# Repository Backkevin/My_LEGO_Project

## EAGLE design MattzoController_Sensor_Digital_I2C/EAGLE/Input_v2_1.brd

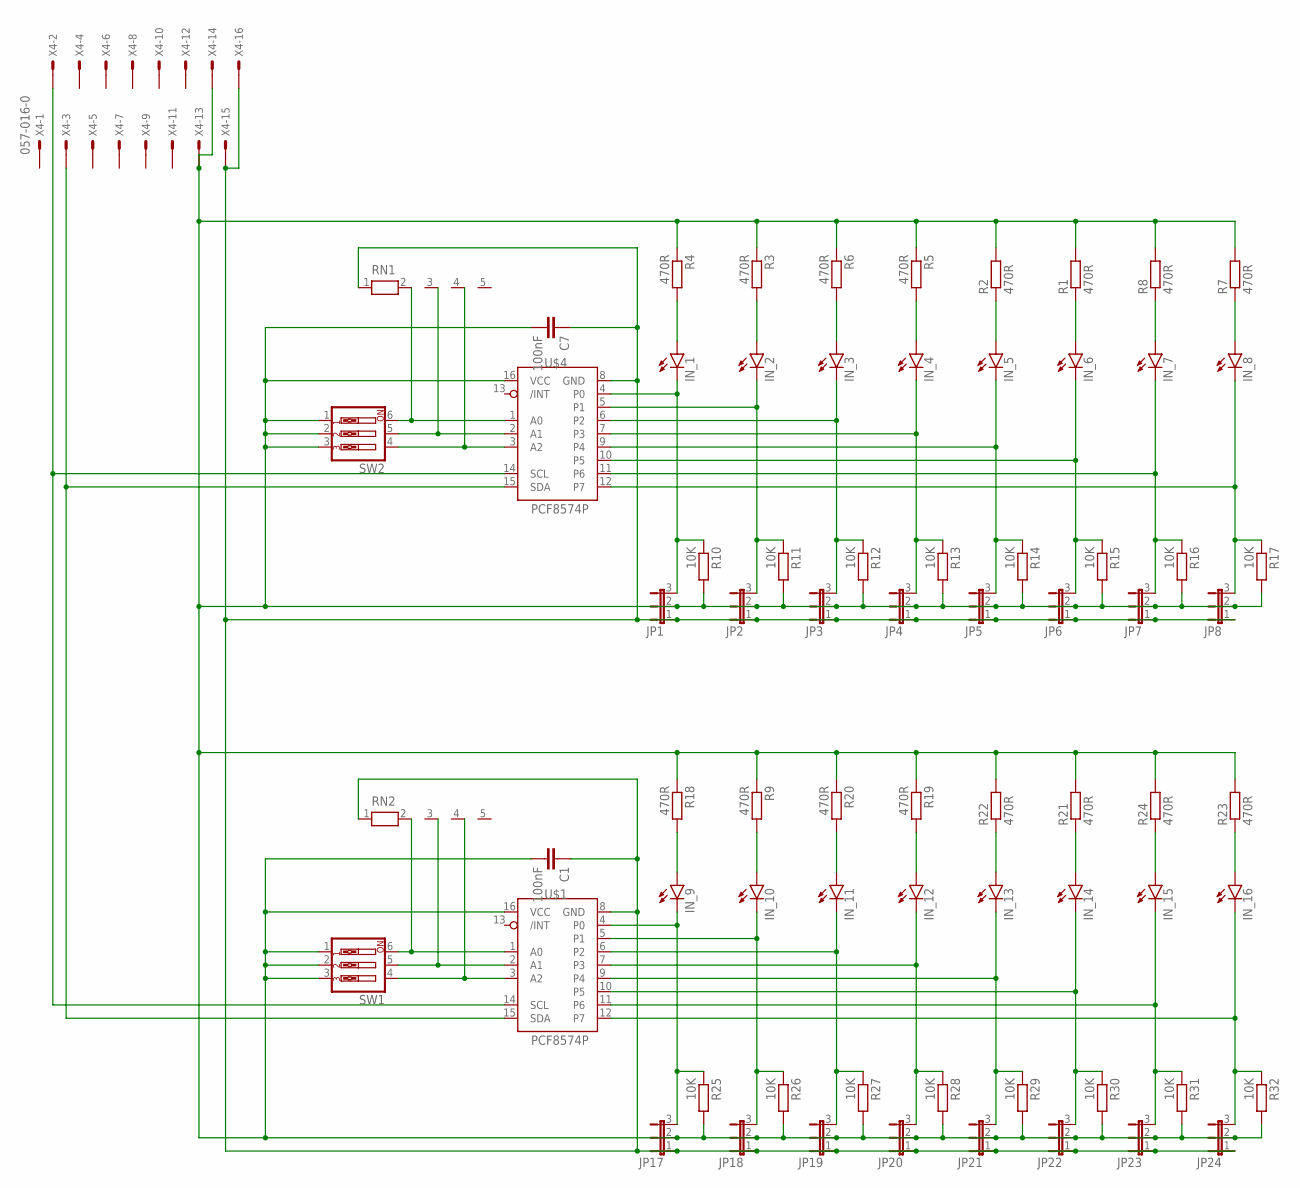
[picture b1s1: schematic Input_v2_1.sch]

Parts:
C1, C7: 100nF; C025-024X044
IN_1, IN_2, IN_3, IN_4, IN_5, IN_6, IN_7, IN_8, IN_9, IN_10, IN_11, IN_12, IN_13, IN_14, IN_15, IN_16: LED3MM
JP1, JP2, JP3, JP4, JP5, JP6, JP7, JP8, JP17, JP18, JP19, JP20, JP21, JP22, JP23, JP24: JP2E; JP2
R1, R2, R3, R4, R5, R6, R7, R8, R9, R18, R19, R20, R21, R22, R23, R24: 470R; 0309/10
R10, R11, R12, R13, R14, R15, R16, R17, R25, R26, R27, R28, R29, R30, R31, R32: 10K; 0309/10
RN1, RN2: RN04; RN-5
SW1, SW2: SW_DIP-3; EDG-03
U$1, U$4: PCF8574P; DIL16
X4: 057-016-0

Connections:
GND2: C1.1, C7.1, JP1.1, JP2.1, JP3.1, JP4.1, JP5.1, JP6.1, JP7.1, JP8.1, JP17.1, JP18.1, JP19.1, JP20.1, JP21.1, JP22.1, JP23.1, JP24.1, RN1.1, RN2.1, U$1.8 (GND), U$4.8 (GND), X4.15, X4.16
unnamed: IN_8.A, R7.1
unnamed: IN_7.A, R8.1
unnamed: IN_6.A, R1.1
unnamed: IN_5.A, R2.1
unnamed: IN_4.A, R5.2
unnamed: IN_3.A, R6.2
unnamed: IN_2.A, R3.2
unnamed: IN_1.A, R4.2
unnamed: RN2.4, SW1.4, U$1.3 (A2)
unnamed: RN2.3, SW1.5, U$1.2 (A1)
unnamed: RN2.2, SW1.6, U$1.1 (A0)
unnamed: RN1.2, SW2.6, U$4.1 (A0)
unnamed: RN1.3, SW2.5, U$4.2 (A1)
unnamed: RN1.4, SW2.4, U$4.3 (A2)
unnamed: IN_9.K (C), JP17.3, R25.1, U$1.4 (P0)
unnamed: IN_10.K (C), JP18.3, R26.1, U$1.5 (P1)
unnamed: IN_11.K (C), JP19.3, R27.1, U$1.6 (P2)
unnamed: IN_1.K (C), JP1.3, R10.1, U$4.4 (P0)
unnamed: IN_2.K (C), JP2.3, R11.1, U$4.5 (P1)
unnamed: IN_3.K (C), JP3.3, R12.1, U$4.6 (P2)
unnamed: IN_4.K (C), JP4.3, R13.1, U$4.7 (P3)
unnamed: IN_5.K (C), JP5.3, R14.1, U$4.9 (P4)
unnamed: IN_6.K (C), JP6.3, R15.1, U$4.10 (P5)
unnamed: IN_7.K (C), JP7.3, R16.1, U$4.11 (P6)
unnamed: IN_8.K (C), JP8.3, R17.1, U$4.12 (P7)
unnamed: IN_12.K (C), JP20.3, R28.1, U$1.7 (P3)
unnamed: IN_13.K (C), JP21.3, R29.1, U$1.9 (P4)
unnamed: IN_14.K (C), JP22.3, R30.1, U$1.10 (P5)
unnamed: IN_15.K (C), JP23.3, R31.1, U$1.11 (P6)
unnamed: IN_16.K (C), JP24.3, R32.1, U$1.12 (P7)
unnamed: IN_16.A, R23.1
unnamed: IN_15.A, R24.1
unnamed: IN_14.A, R21.1
unnamed: IN_13.A, R22.1
unnamed: IN_12.A, R19.2
unnamed: IN_11.A, R20.2
unnamed: IN_10.A, R9.2
unnamed: IN_9.A, R18.2
unnamed: U$1.15 (SDA), U$4.15 (SDA), X4.3
SCL: U$1.14 (SCL), U$4.14 (SCL), X4.2
VCC5.1: C1.2, C7.2, JP1.2, JP2.2, JP3.2, JP4.2, JP5.2, JP6.2, JP7.2, JP8.2, JP17.2, JP18.2, JP19.2, JP20.2, JP21.2, JP22.2, JP23.2, JP24.2, R1.2, R2.2, R3.1, R4.1, R5.1, R6.1, R7.2, R8.2, R9.1, R10.2, R11.2, R12.2, R13.2, R14.2, R15.2, R16.2, R17.2, R18.1, R19.1, R20.1, R21.2, R22.2, R23.2, R24.2, R25.2, R26.2, R27.2, R28.2, R29.2, R30.2, R31.2, R32.2, SW1.1, SW1.2, SW1.3, SW2.1, SW2.2, SW2.3, U$1.16 (VCC), U$4.16 (VCC), X4.13, X4.14

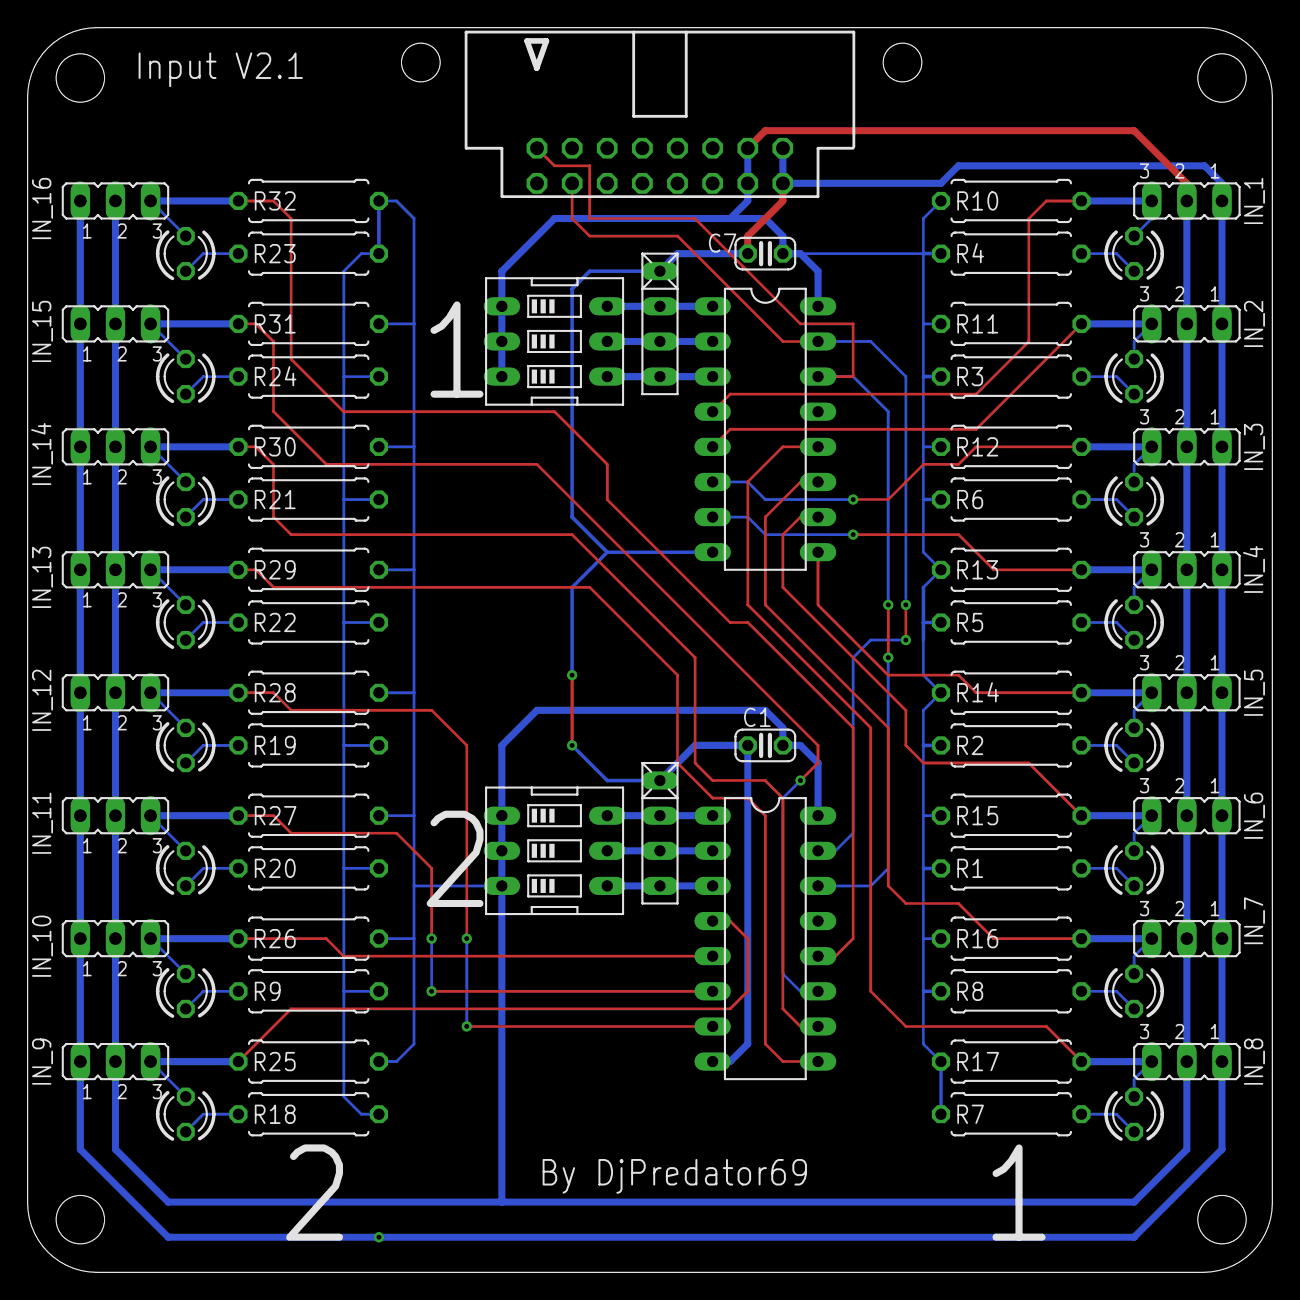
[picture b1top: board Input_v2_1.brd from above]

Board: 2 copper layers, 90.0 x 90.0 mm, 73 parts (0 on the bottom side), 42 nets.

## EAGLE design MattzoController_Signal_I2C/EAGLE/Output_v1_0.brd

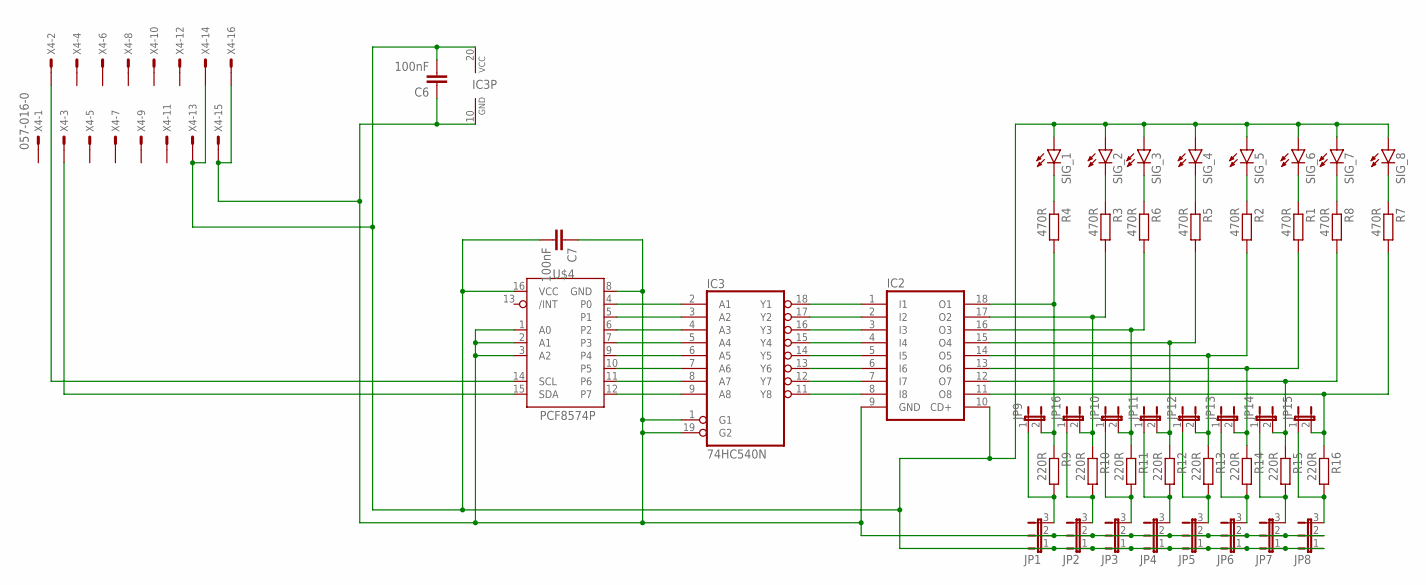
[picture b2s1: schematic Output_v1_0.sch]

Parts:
C6, C7: 100nF; C025-024X044
IC2: ULN2803A; DIL18
IC3: 74HC540N; DIL20
JP1, JP2, JP3, JP4, JP5, JP6, JP7, JP8: JP2E; JP2
JP9, JP10, JP11, JP12, JP13, JP14, JP15, JP16: JP1E; JP1
R1, R2, R3, R4, R5, R6, R7, R8: 470R; 0309/10
R9, R10, R11, R12, R13, R14, R15, R16: 220R; 0309/10
SIG_1, SIG_2, SIG_3, SIG_4, SIG_5, SIG_6, SIG_7, SIG_8: LED3MM
U$4: PCF8574P; DIL16
X4: 057-016-0

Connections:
GND1: C6.1, C7.1, IC2.9 (GND), IC3.1 (G1), IC3.10 (GND), IC3.19 (G2), JP1.2, JP2.2, JP3.2, JP4.2, JP5.2, JP6.2, JP7.2, JP8.2, U$4.1 (A0), U$4.2 (A1), U$4.3 (A2), U$4.8 (GND), X4.15, X4.16
unnamed: JP1.3, JP9.1, R9.2
unnamed: IC2.13 (O6), JP13.2, R1.2, R14.1
unnamed: R2.1, SIG_5.K (C)
unnamed: R1.1, SIG_6.K (C)
unnamed: IC2.12 (O7), JP14.2, R8.2, R15.1
unnamed: U$4.15 (SDA), X4.3
unnamed: R8.1, SIG_7.K (C)
unnamed: R7.1, SIG_8.K (C)
unnamed: JP2.3, JP16.1, R10.2
unnamed: JP3.3, JP10.1, R11.2
unnamed: JP4.3, JP11.1, R12.2
unnamed: IC2.8 (I8), IC3.11 (Y8)
unnamed: JP5.3, JP12.1, R13.2
unnamed: IC2.7 (I7), IC3.12 (Y7)
unnamed: IC2.6 (I6), IC3.13 (Y6)
unnamed: IC2.5 (I5), IC3.14 (Y5)
unnamed: IC2.4 (I4), IC3.15 (Y4)
unnamed: IC2.3 (I3), IC3.16 (Y3)
unnamed: IC2.2 (I2), IC3.17 (Y2)
unnamed: IC2.1 (I1), IC3.18 (Y1)
unnamed: IC3.2 (A1), U$4.4 (P0)
unnamed: IC3.3 (A2), U$4.5 (P1)
unnamed: IC3.4 (A3), U$4.6 (P2)
unnamed: IC3.5 (A4), U$4.7 (P3)
unnamed: IC3.6 (A5), U$4.9 (P4)
unnamed: IC3.7 (A6), U$4.10 (P5)
unnamed: IC3.8 (A7), U$4.11 (P6)
unnamed: IC3.9 (A8), U$4.12 (P7)
unnamed: IC2.18 (O1), JP9.2, R4.2, R9.1
unnamed: JP6.3, JP13.1, R14.2
unnamed: IC2.17 (O2), JP16.2, R3.2, R10.1
unnamed: JP7.3, JP14.1, R15.2
unnamed: JP8.3, JP15.1, R16.2
unnamed: U$4.14 (SCL), X4.2
unnamed: R4.1, SIG_1.K (C)
unnamed: R3.1, SIG_2.K (C)
unnamed: IC2.11 (O8), JP15.2, R7.2, R16.1
unnamed: IC2.16 (O3), JP10.2, R6.2, R11.1
unnamed: IC2.15 (O4), JP11.2, R5.2, R12.1
unnamed: IC2.14 (O5), JP12.2, R2.2, R13.1
unnamed: R6.1, SIG_3.K (C)
unnamed: R5.1, SIG_4.K (C)
VCC5.0: C6.2, C7.2, IC2.10 (CD+), IC3.20 (VCC), JP1.1, JP2.1, JP3.1, JP4.1, JP5.1, JP6.1, JP7.1, JP8.1, SIG_1.A, SIG_2.A, SIG_3.A, SIG_4.A, SIG_5.A, SIG_6.A, SIG_7.A, SIG_8.A, U$4.16 (VCC), X4.13, X4.14

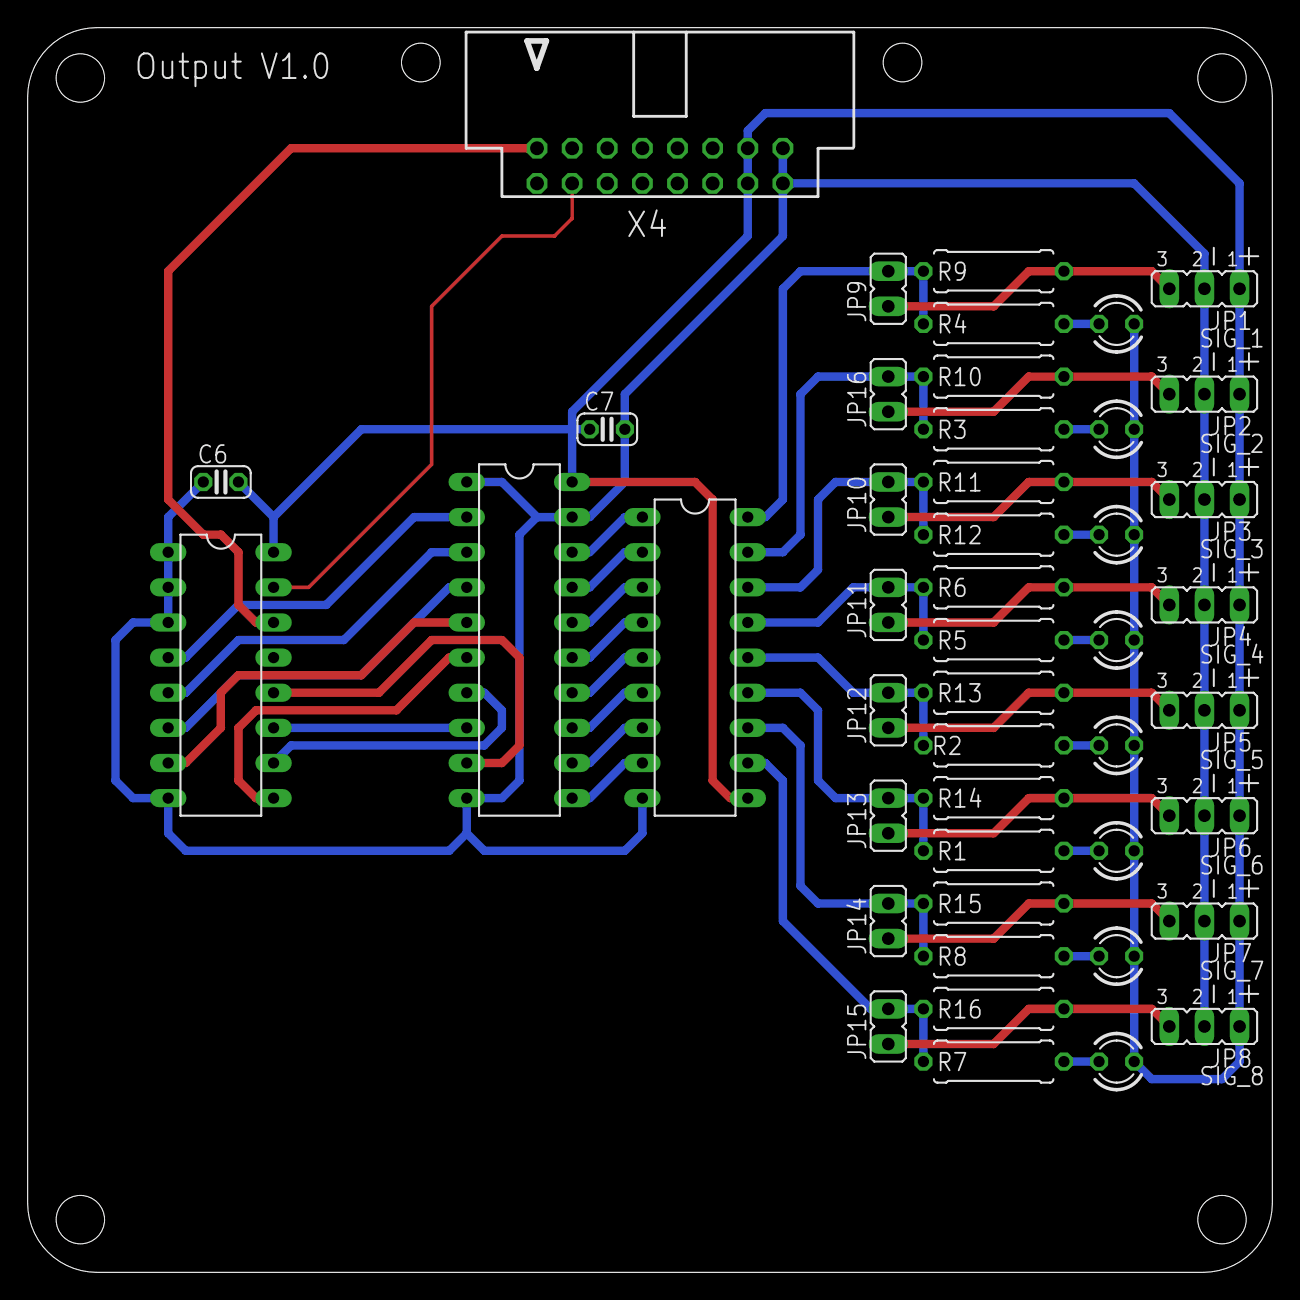
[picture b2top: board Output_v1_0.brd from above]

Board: 2 copper layers, 90.0 x 90.0 mm, 46 parts (0 on the bottom side), 44 nets.

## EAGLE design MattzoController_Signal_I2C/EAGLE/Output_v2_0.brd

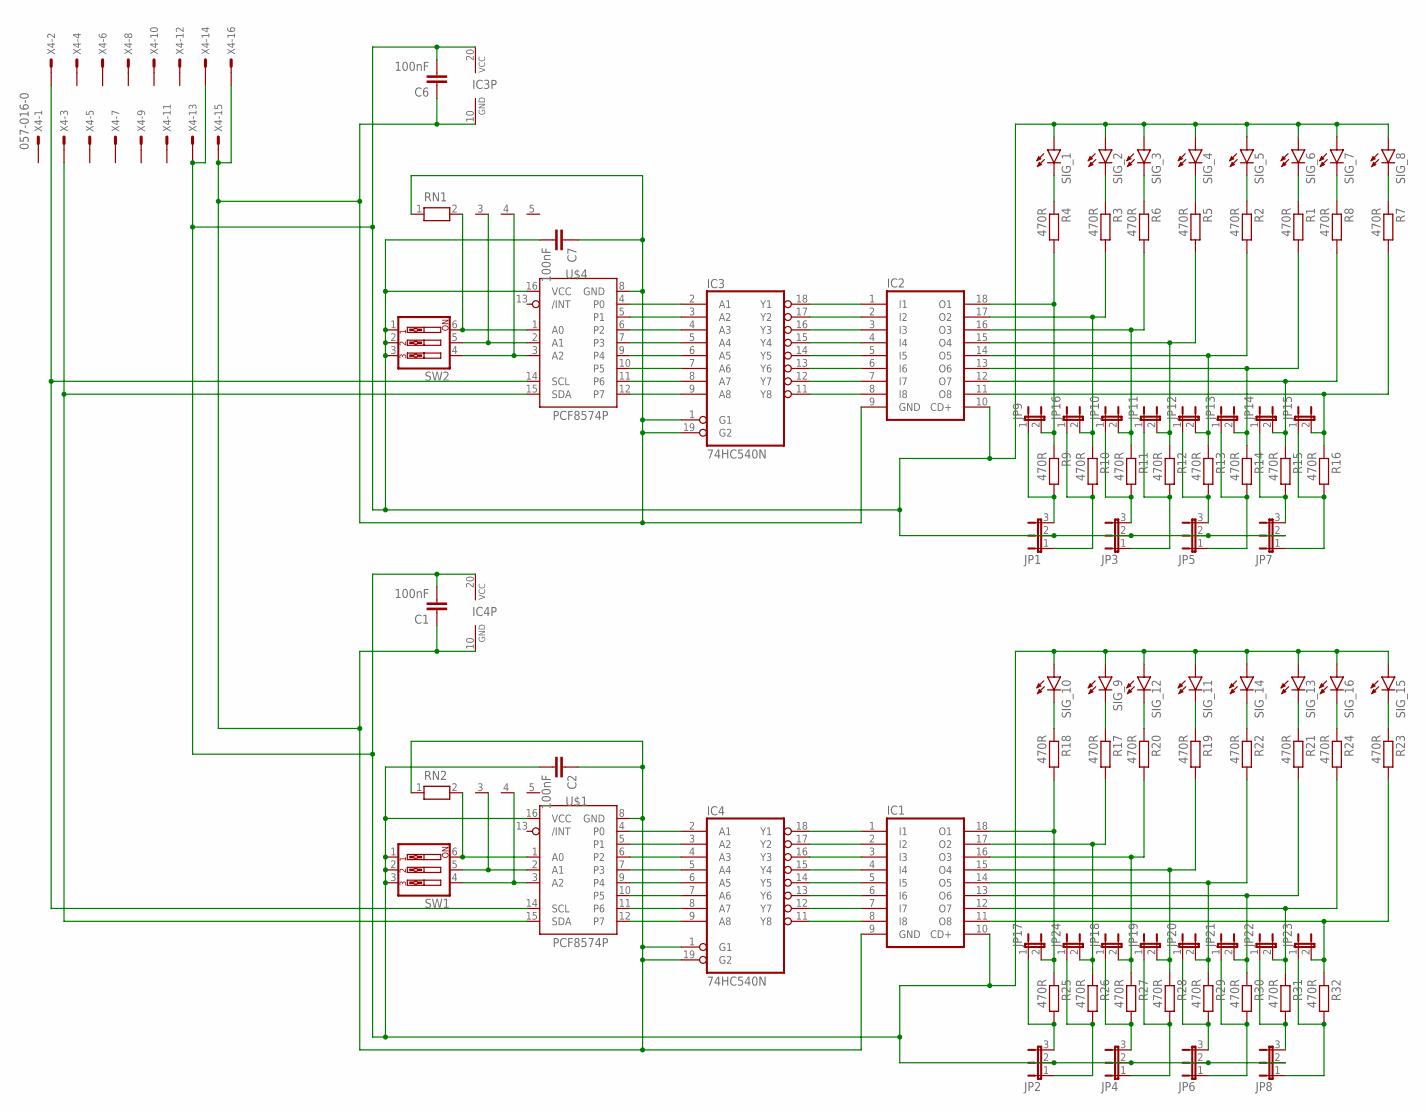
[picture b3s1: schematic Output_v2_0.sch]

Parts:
C1, C2, C6, C7: 100nF; C025-024X044
IC1, IC2: ULN2803A; DIL18
IC3, IC4: 74HC540N; DIL20
JP1, JP2, JP3, JP4, JP5, JP6, JP7, JP8: JP2E; JP2
JP9, JP10, JP11, JP12, JP13, JP14, JP15, JP16, JP17, JP18, JP19, JP20, JP21, JP22, JP23, JP24: JP1E; JP1
R1, R2, R3, R4, R5, R6, R7, R8, R9, R10, R11, R12, R13, R14, R15, R16, R17, R18, R19, R20, R21, R22, R23, R24, R25, R26, R27, R28, R29, R30, R31, R32: 470R; 0309/10
RN1, RN2: RN04; RN-5
SIG_1, SIG_2, SIG_3, SIG_4, SIG_5, SIG_6, SIG_7, SIG_8, SIG_9, SIG_10, SIG_11, SIG_12, SIG_13, SIG_14, SIG_15, SIG_16: LED3MM
SW1, SW2: SW_DIP-3; EDG-03
U$1, U$4: PCF8574P; DIL16
X4: 057-016-0

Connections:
GND2: C1.1, C2.1, C6.1, C7.1, IC1.9 (GND), IC2.9 (GND), IC3.1 (G1), IC3.10 (GND), IC3.19 (G2), IC4.1 (G1), IC4.10 (GND), IC4.19 (G2), RN1.1, RN2.1, U$1.8 (GND), U$4.8 (GND), X4.15, X4.16
unnamed: JP1.3, JP9.1, R9.2
unnamed: IC2.13 (O6), JP13.2, R1.2, R14.1
unnamed: R2.1, SIG_5.K (C)
unnamed: R1.1, SIG_6.K (C)
unnamed: IC2.12 (O7), JP14.2, R8.2, R15.1
unnamed: RN2.4, SW1.4, U$1.3 (A2)
unnamed: R8.1, SIG_7.K (C)
unnamed: R7.1, SIG_8.K (C)
unnamed: JP1.1, JP16.1, R10.2
unnamed: JP3.3, JP10.1, R11.2
unnamed: JP3.1, JP11.1, R12.2
unnamed: IC2.8 (I8), IC3.11 (Y8)
unnamed: JP5.3, JP12.1, R13.2
unnamed: IC2.7 (I7), IC3.12 (Y7)
unnamed: IC2.6 (I6), IC3.13 (Y6)
unnamed: IC2.5 (I5), IC3.14 (Y5)
unnamed: IC2.4 (I4), IC3.15 (Y4)
unnamed: IC2.3 (I3), IC3.16 (Y3)
unnamed: IC2.2 (I2), IC3.17 (Y2)
unnamed: IC2.1 (I1), IC3.18 (Y1)
unnamed: IC3.2 (A1), U$4.4 (P0)
unnamed: IC3.3 (A2), U$4.5 (P1)
unnamed: IC3.4 (A3), U$4.6 (P2)
unnamed: IC3.5 (A4), U$4.7 (P3)
unnamed: IC3.6 (A5), U$4.9 (P4)
unnamed: IC3.7 (A6), U$4.10 (P5)
unnamed: IC3.8 (A7), U$4.11 (P6)
unnamed: IC3.9 (A8), U$4.12 (P7)
unnamed: IC2.18 (O1), JP9.2, R4.2, R9.1
unnamed: JP5.1, JP13.1, R14.2
unnamed: IC2.17 (O2), JP16.2, R3.2, R10.1
unnamed: JP7.3, JP14.1, R15.2
unnamed: JP7.1, JP15.1, R16.2
unnamed: IC1.8 (I8), IC4.11 (Y8)
unnamed: RN2.3, SW1.5, U$1.2 (A1)
unnamed: R4.1, SIG_1.K (C)
unnamed: R3.1, SIG_2.K (C)
unnamed: IC2.11 (O8), JP15.2, R7.2, R16.1
unnamed: IC1.7 (I7), IC4.12 (Y7)
unnamed: IC1.6 (I6), IC4.13 (Y6)
unnamed: IC2.16 (O3), JP10.2, R6.2, R11.1
unnamed: IC2.15 (O4), JP11.2, R5.2, R12.1
unnamed: IC2.14 (O5), JP12.2, R2.2, R13.1
unnamed: IC1.5 (I5), IC4.14 (Y5)
unnamed: IC1.4 (I4), IC4.15 (Y4)
unnamed: IC1.3 (I3), IC4.16 (Y3)
unnamed: IC1.2 (I2), IC4.17 (Y2)
unnamed: IC1.1 (I1), IC4.18 (Y1)
unnamed: IC4.2 (A1), U$1.4 (P0)
unnamed: IC4.3 (A2), U$1.5 (P1)
unnamed: IC4.4 (A3), U$1.6 (P2)
unnamed: IC4.5 (A4), U$1.7 (P3)
unnamed: R6.1, SIG_3.K (C)
unnamed: R5.1, SIG_4.K (C)
unnamed: IC4.6 (A5), U$1.9 (P4)
unnamed: IC4.7 (A6), U$1.10 (P5)
unnamed: IC4.8 (A7), U$1.11 (P6)
unnamed: IC4.9 (A8), U$1.12 (P7)
unnamed: IC1.18 (O1), JP17.2, R18.2, R25.1
unnamed: IC1.17 (O2), JP24.2, R17.2, R26.1
unnamed: R18.1, SIG_10.K (C)
unnamed: R17.1, SIG_9.K (C)
unnamed: IC1.16 (O3), JP18.2, R20.2, R27.1
unnamed: IC1.15 (O4), JP19.2, R19.2, R28.1
unnamed: IC1.14 (O5), JP20.2, R22.2, R29.1
unnamed: R20.1, SIG_12.K (C)
unnamed: R19.1, SIG_11.K (C)
unnamed: IC1.13 (O6), JP21.2, R21.2, R30.1
unnamed: R22.1, SIG_14.K (C)
unnamed: R21.1, SIG_13.K (C)
unnamed: IC1.12 (O7), JP22.2, R24.2, R31.1
unnamed: R24.1, SIG_16.K (C)
unnamed: R23.1, SIG_15.K (C)
unnamed: JP2.3, JP17.1, R25.2
unnamed: JP2.1, JP24.1, R26.2
unnamed: JP4.3, JP18.1, R27.2
unnamed: JP4.1, JP19.1, R28.2
unnamed: JP6.3, JP20.1, R29.2
unnamed: JP6.1, JP21.1, R30.2
unnamed: JP8.3, JP22.1, R31.2
unnamed: JP8.1, JP23.1, R32.2
unnamed: U$1.14 (SCL), U$4.14 (SCL), X4.2
unnamed: IC1.11 (O8), JP23.2, R23.2, R32.1
unnamed: U$1.15 (SDA), U$4.15 (SDA), X4.3
unnamed: RN2.2, SW1.6, U$1.1 (A0)
unnamed: RN1.2, SW2.6, U$4.1 (A0)
unnamed: RN1.3, SW2.5, U$4.2 (A1)
unnamed: RN1.4, SW2.4, U$4.3 (A2)
VCC5.1: C1.2, C2.2, C6.2, C7.2, IC1.10 (CD+), IC2.10 (CD+), IC3.20 (VCC), IC4.20 (VCC), JP1.2, JP2.2, JP3.2, JP4.2, JP5.2, JP6.2, JP7.2, JP8.2, SIG_1.A, SIG_2.A, SIG_3.A, SIG_4.A, SIG_5.A, SIG_6.A, SIG_7.A, SIG_8.A, SIG_9.A, SIG_10.A, SIG_11.A, SIG_12.A, SIG_13.A, SIG_14.A, SIG_15.A, SIG_16.A, SW1.1, SW1.2, SW1.3, SW2.1, SW2.2, SW2.3, U$1.16 (VCC), U$4.16 (VCC), X4.13, X4.14

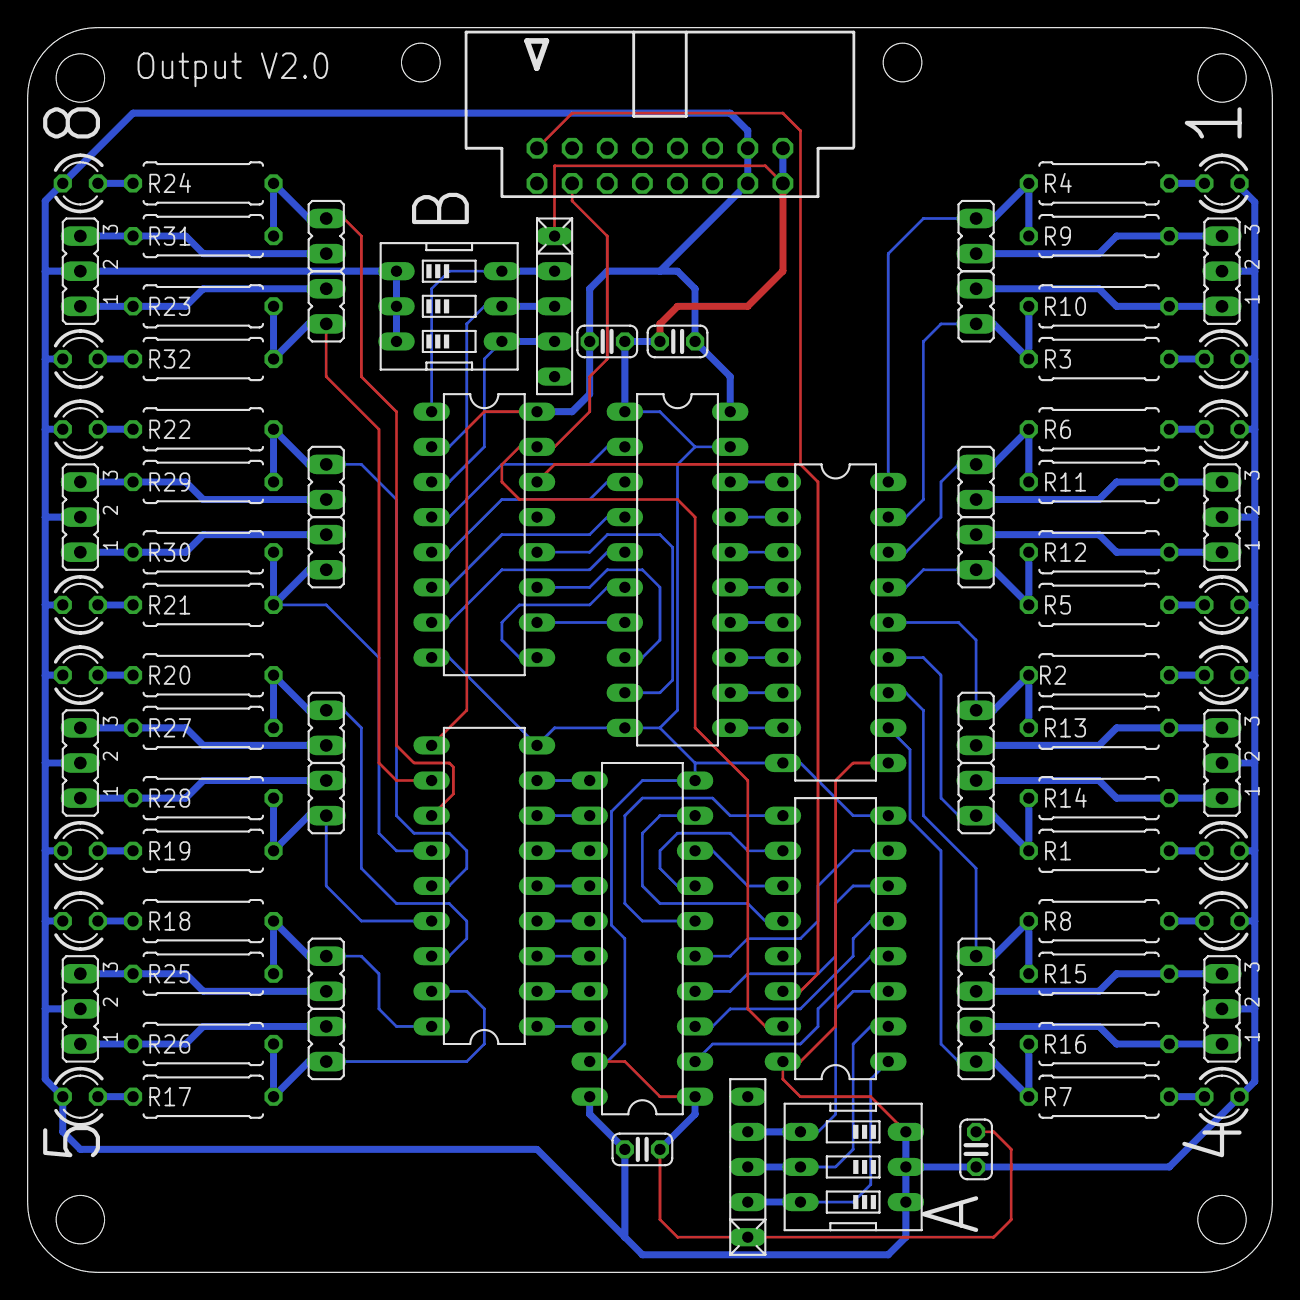
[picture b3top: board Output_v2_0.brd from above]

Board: 2 copper layers, 90.0 x 90.0 mm, 87 parts (0 on the bottom side), 90 nets.

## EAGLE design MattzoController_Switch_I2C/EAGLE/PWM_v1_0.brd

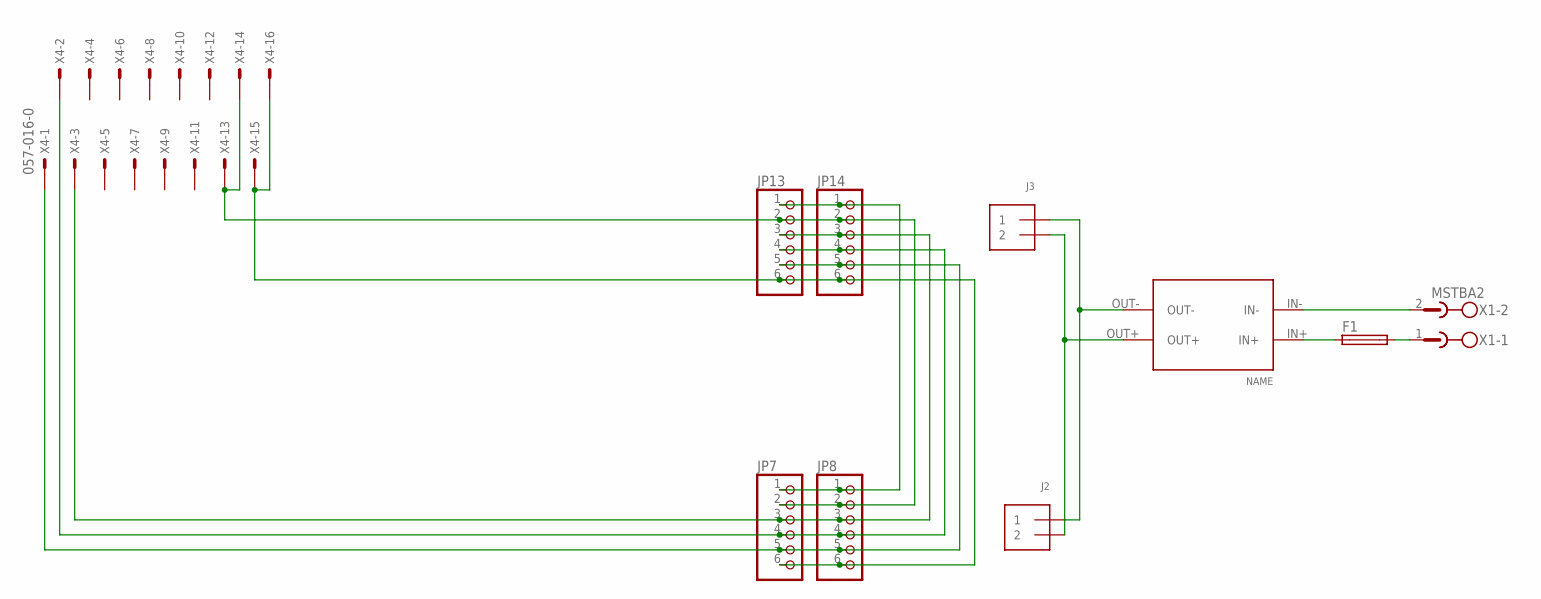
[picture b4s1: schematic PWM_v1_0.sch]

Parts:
F1: SH25
J2, J3: TERMBLOCK_1X2; TERMBLOCK_1X2-3.5MM
JP7, JP8, JP13, JP14: PINHD-1X6CB; 1X06-CLEANBIG
U$2: CP8-ADJ
X1: MSTBA2
X4: 057-016-0

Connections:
unnamed: J2.2, J3.2, U$2.OUT+
unnamed: J2.1, J3.1, U$2.OUT-
unnamed: JP7.4, JP8.4, JP13.4, JP14.4, X4.2
unnamed: JP7.5, JP8.5, JP13.5, JP14.5, X4.1
unnamed: JP7.6, JP8.6, JP13.6, JP14.6, X4.15, X4.16
unnamed: JP7.1, JP8.1, JP13.1, JP14.1
unnamed: JP7.2, JP8.2, JP13.2, JP14.2, X4.13, X4.14
unnamed: U$2.IN-, X1.2
unnamed: F1.1, U$2.IN+
unnamed: F1.2, X1.1
unnamed: JP7.3, JP8.3, JP13.3, JP14.3, X4.3

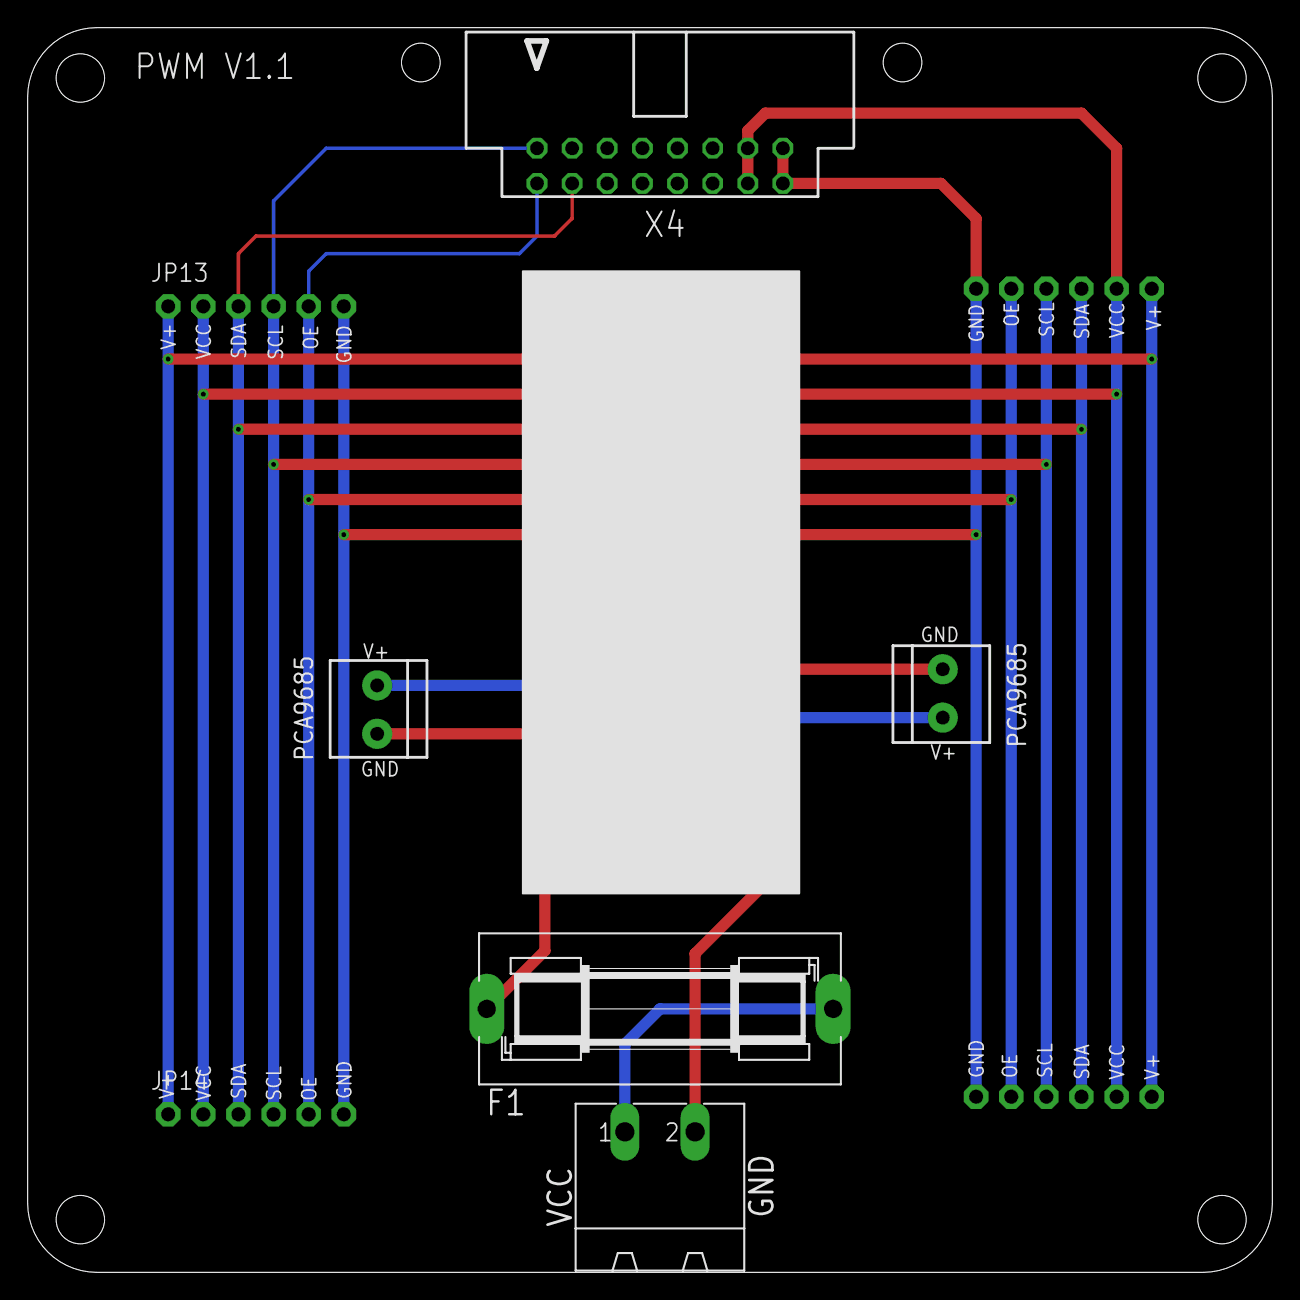
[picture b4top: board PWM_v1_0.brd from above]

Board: 2 copper layers, 90.0 x 90.0 mm, 10 parts (0 on the bottom side), 11 nets.
